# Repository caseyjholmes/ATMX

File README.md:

# ATMX
4HP Eurorack Attenumixer/multiple.

Mix. Attenuate. Multply. Add. Subtract. Cheap, Easy!
Better than using multiples alone!

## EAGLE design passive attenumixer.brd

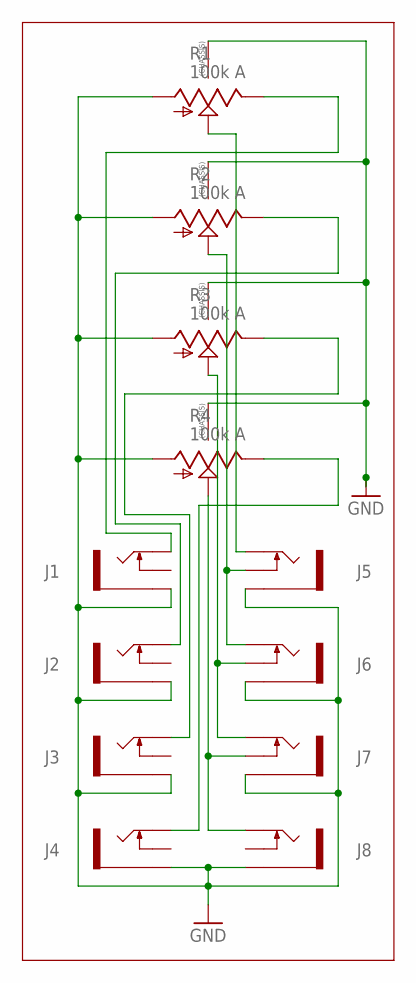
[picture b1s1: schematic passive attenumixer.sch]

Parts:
J1, J2, J3, J4, J5, J6, J7, J8: THONKICONNNEW; WQP-PJ301M-12_JACK
R1, R2, R3, R4: 100k A; 9MM_SNAP-IN_POT

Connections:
GND: J1.P$3_SLEEVE (SLEEVE), J2.P$3_SLEEVE (SLEEVE), J3.P$3_SLEEVE (SLEEVE), J4.P$3_SLEEVE (SLEEVE), J5.P$3_SLEEVE (SLEEVE), J6.P$3_SLEEVE (SLEEVE), J7.P$3_SLEEVE (SLEEVE), J8.P$3_SLEEVE (SLEEVE), R1.1 (A), R1.CHASSIS1, R1.CHASSIS2, R2.1 (A), R2.CHASSIS1, R2.CHASSIS2, R3.1 (A), R3.CHASSIS1, R3.CHASSIS2, R4.1 (A), R4.CHASSIS1, R4.CHASSIS2
unnamed: J5.P$1_TIP (TIP), R1.2 (S)
unnamed: J7.P$2_SWITCH (SWITCH), J8.P$1_TIP (TIP), R4.2 (S)
unnamed: J6.P$2_SWITCH (SWITCH), J7.P$1_TIP (TIP), R3.2 (S)
unnamed: J5.P$2_SWITCH (SWITCH), J6.P$1_TIP (TIP), R2.2 (S)
unnamed: J1.P$1_TIP (TIP), R1.3 (E)
unnamed: J2.P$1_TIP (TIP), R2.3 (E)
unnamed: J3.P$1_TIP (TIP), R3.3 (E)
unnamed: J4.P$1_TIP (TIP), R4.3 (E)

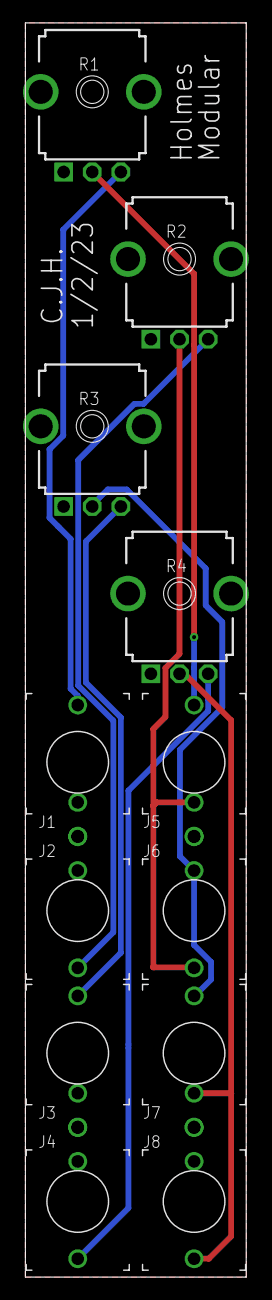
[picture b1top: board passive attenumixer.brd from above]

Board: 2 copper layers, 19.3 x 109.5 mm, 12 parts (0 on the bottom side), 9 nets.
